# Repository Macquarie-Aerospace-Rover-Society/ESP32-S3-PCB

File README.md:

# Custom ESP32-S3 WROOM DevKit

This repo is for custom ESP32-S3 WROOM devkits, the plan is to add a ov5640 / ov2640 along with an SD card. Then use JLCPCB color printing to produce a colorful board that is also fit for MARS needs.

## Snapshot

This should remain up to date thanks to the CI workflow.

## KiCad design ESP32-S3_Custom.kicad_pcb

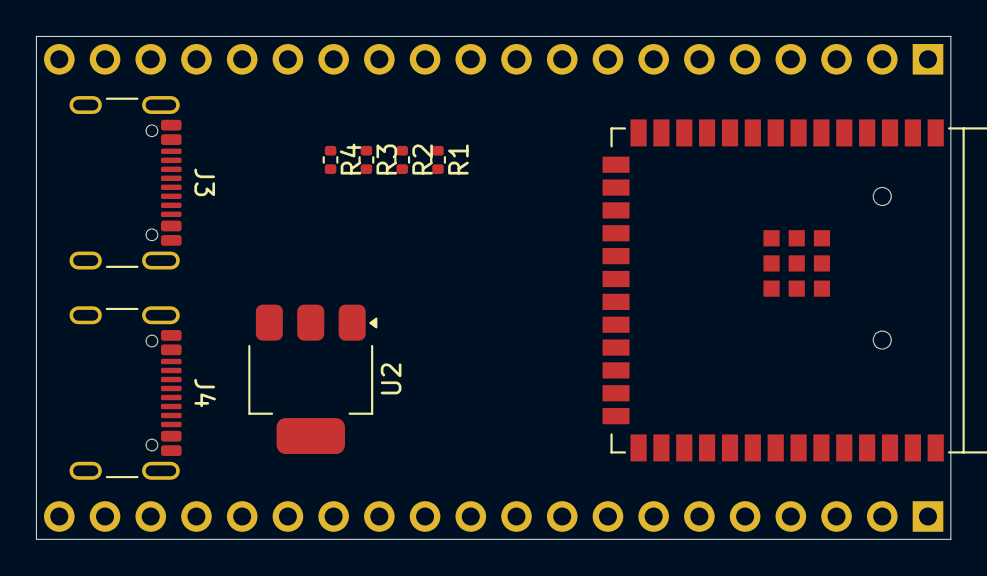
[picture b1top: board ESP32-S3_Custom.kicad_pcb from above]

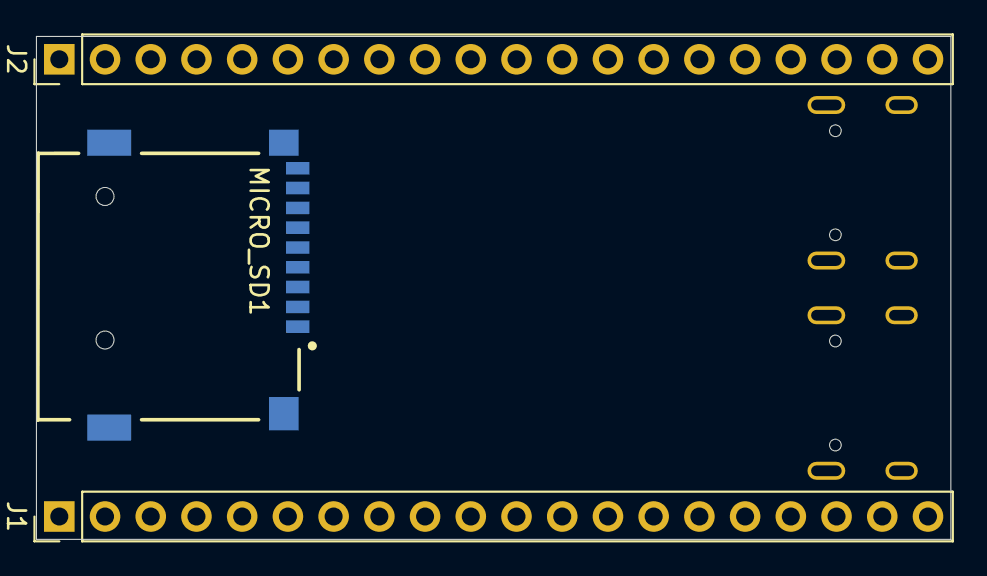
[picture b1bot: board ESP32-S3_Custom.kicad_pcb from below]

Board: 2 copper layers, 50.8 x 27.9 mm, 11 parts (3 on the bottom side), 14 nets, no tracks yet.

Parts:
J1, J2: Conn_01x20_Pin; PinHeader_1x20_P2.54mm_Vertical
J3, J4: USB_C_Receptacle_USB2.0_16P; USB_C_Receptacle_GCT_USB4105-xx-A_16P_TopMnt_Horizontal
MICRO_SD1: TF-01A
R1, R2, R3, R4: 4k7 0402; R_0402_1005Metric
U1: ESP32-S3-WROOM-1
U2: AMS1117-3.3; SOT-223-3_TabPin2

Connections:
unnamed: J3.A5 (CC1), R1.1
unnamed: J3.B5 (CC2), R2.1
unnamed: J3.A6 (D+), J3.B6 (D+)
unnamed: J3.A7 (D-), J3.B7 (D-)
unnamed: J3.A1 (GND), J3.A12 (GND), J3.B1 (GND), J3.B12 (GND)
unnamed: J3.A4 (VBUS), J3.A9 (VBUS), J3.B4 (VBUS), J3.B9 (VBUS)
unnamed: J4.A5 (CC1), R3.1
unnamed: J4.B5 (CC2), R4.1
unnamed: J4.A6 (D+), J4.B6 (D+)
unnamed: J4.A7 (D-), J4.B7 (D-)
unnamed: J4.A1 (GND), J4.A12 (GND), J4.B1 (GND), J4.B12 (GND)
unnamed: J4.A4 (VBUS), J4.A9 (VBUS), J4.B4 (VBUS), J4.B9 (VBUS)
unnamed: U1.1 (GND), U1.40 (GND), U1.41 (GND)
SHIELD: MICRO_SD1.MP1 (SHIELD), MICRO_SD1.MP2 (SHIELD), MICRO_SD1.MP3 (SHIELD), MICRO_SD1.MP4 (SHIELD)

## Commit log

2026-01-04 Added components
    - USB-C connectors
2026-01-04 Add MIT License to the project
2026-01-04 Added TF-01A component
    - Added local library support.
    - linked component correctly.
    NOTE: proj_foot was not the default for snap.
    TODO: Ensure ESP32-S3 WROOM ports correctly
2026-01-04 workflow for rendering
2026-01-04 Update KiCad installation commands in workflow
2026-01-04 Update 3D render workflow to use ESP32-S3_Custom
2026-01-04 Enable write permissions for workflow job
    Added permissions to allow job to push commits.
2026-01-04 Update 3D renders [skip ci]
2026-01-04 Limit workflow triggers to ESP32-S3_Custom.kicad_pcb
    Restrict workflow triggers to specific paths for pushes and pull requests.
2026-01-04 Added README
2026-01-05 Adjusted 3D model for USB-C connectors
2026-01-09 Shuffled some parts around
2026-01-09 any msg
2026-01-10 Rotated PCB 90 degrees so its in landscape
2026-01-17 semidone
2026-02-04 imu update
